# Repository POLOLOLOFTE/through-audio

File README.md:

# through-audio
a custom audio display for seeing how cool is music! compatible with the #free digital amp:

## Description
this is a machine that converts audio signals in visible immagines like a spectrum (Oscilloscope) or a frequencess dividor so you can see the music and admire the beauty of sound!

the hole mashine is controlled by a esp32 though a custom pcb

and it has got two displays: one with led matrix and the other one is a lcd display RGB 3.5" (for using the code it needs to be touch)

> "Note:" This is not a professional equipment and probably is not precise eather.

### why i made it?
as i sayed in the other projects i love music and it's a partof me, and have the opportunity to see it is a magic things!

## Assembly:
- you have to soder every componets to the pcb in the right order
- then you have to put the ESP32 DevC 38Pin in the slot
- after you could upload the firmware (opsional)
- then i raccomend wire up the display by folowing the pcb and then test is something explode😭🤣(just joking) i mean if it works!
- after this you should put the board on the custom case and rewire (use long wires) the displays (and glue them with hot glue)
- after this if you use the display that i will link you should run two wires from the matrix display's button and connect them to a second one and put the second on the front pannel
- then you should connect the 16v power, the usb (only for power) and the jack for the input
- enjoy!

## Input and Output
it has got only input:
- Jack
- 16V screw connector
- and USB (Esp32)

## Settings
it's not that complex but if you use the Default firmware you got the touch on the main display and the button for changing the mode on the odter matrix display
as the Default code you have 3 buttons that you can press 1 is for the theme (colors) one is for the mode that you want(Oscilloscope, equalizor, equalizor matrix like)

# Gallery:

#Bill Of Materials

| # | Component | Qty | Why it is used | Amazon link | Approx. price (USD) |
|---|-----------|-----|----------------|-------------|---------------------|
| 1 | ESP32 DevKit, 38-pin, USB-C (ESP-WROOM-32) | 1 | Main microcontroller. Samples the audio on ADC1 (GPIO34/35), computes the FFT and draws the three display modes. | [DIYables ESP32 38-pin](https://www.amazon.com/dp/B0GQXZ2RK1) | ~$11 |
| 2 | 3.5" TFT 480x320, ILI9488, SPI, resistive touch (stylus included) | 1 | User interface: oscilloscope, spectrum and stereo LED views, with big touch buttons for mode, color and gain. | [Hosyond 3.5" ILI9488](https://www.amazon.com/dp/B0BWJHK4M6) | ~$18 |
| 3 | Dual 12-level stereo LED VU-meter module (7-12 V) | 1 | Hardware LED level bars. They run on their own chip, so they need no GPIO, only the audio signal and 9 V. | [Dual 12-level VU meter](https://www.amazon.com/dp/B01MSYKM52) | ~$10 |
| 4 | L7809CV 9 V linear regulator, TO-220 (pack of 5) | 1 pack | Steps 16 V down to the 9 V the VU-meter needs (about 0.7 W of heat at 100 mA). | [L7809CV x5](https://www.amazon.com/dp/B08JHGS3LT) | ~$9 |
| 5 | LM2596 buck converter module (adjustable) | 1 | Efficient 16 V to 5 V for the ESP32 (VIN) and the display. Set it to 5.0 V with a multimeter before connecting anything. | [LM2596 buck module](https://www.amazon.com/dp/B01MS4D2FO) | ~$7 |
| 6 | 3.5 mm stereo jack, 5-pin PCB mount PJ-313 (pack of 5) | 1 pack | Audio input (left/right) for the ESP32 ADC and the VU-meter. | [uxcell PJ-313 x5](https://www.amazon.com/dp/B0BJJGXSJP) | ~$6 |
| 7 | 5.08 mm screw terminal blocks, 2-pin and 5-pin kit | 1 kit | 2-pin: 16 V power input. 5-pin: connection to the VU-meter (L, G, R, G, U). | [Terminal block kit](https://www.amazon.com/dp/B0F7Y1XMWT) | ~$11 |
| 8 | Metal film resistor assortment, 1/4 W 1% | 1 kit | 2x 100 kΩ (audio bias divider), 2x 1 kΩ (ADC input protection), 2x 1-10 kΩ (VU-meter inputs). | [BOJACK resistor kit](https://www.amazon.com/dp/B07P3MFG5D) | ~$13 |
| 9 | Electrolytic capacitor assortment (1 µF to 1000 µF) | 1 kit | Input and output smoothing for the 9 V regulator, and the 16 V input reservoir. Use 25 V or higher. | [Electrolytic kit](https://www.amazon.com/dp/B098RMS3S5) | ~$13 |
| 10 | Ceramic capacitor assortment (0.1 µF to 10 µF) | 1 kit | 100 nF decoupling for the regulator, 1-10 µF audio coupling and bias-node capacitors. | [BOJACK ceramic kit](https://www.amazon.com/dp/B07P7HRGT9) | ~$10 |
| 11 | 2.54 mm single-row female header strips, 40-pin (pack of 20) | 1 pack | Sockets for the ESP32 board and the display, so nothing is soldered directly. Cut to length. | [Female headers 1x40](https://www.amazon.com/dp/B0GXKSB3VF) | ~$8 |
| 12 | TO-220 heatsink + mounting kit (optional) | 1 pack | Keeps the L7809 cool if the VU-meter runs for long periods. | [TO-220 heatsink kit](https://www.amazon.com/dp/B078ZXZ1GN) | ~$8 |

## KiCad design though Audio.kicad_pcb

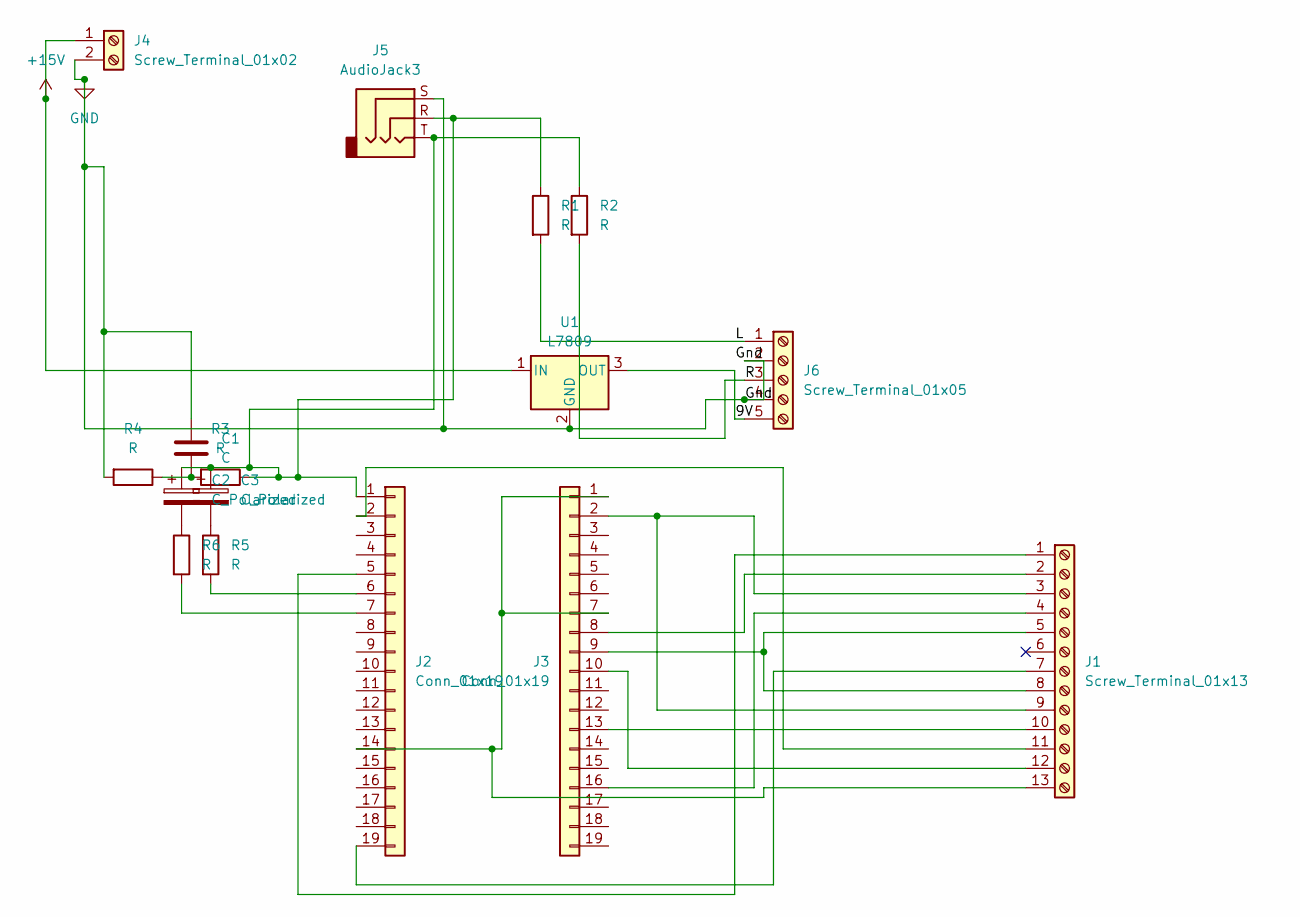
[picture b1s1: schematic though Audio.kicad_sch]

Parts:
C1: C; C_Rect_L18.0mm_W7.0mm_P15.00mm_FKS3_FKP3
C2, C3: C_Polarized; CP_Radial_Tantal_D5.0mm_P5.00mm
J1: Screw_Terminal_01x13; TerminalBlock_MaiXu_MX126-5.0-13P_1x13_P5.00mm
J2, J3: Conn_01x19; PinHeader_1x19_P2.54mm_Vertical
J4: Screw_Terminal_01x02; TerminalBlock_MaiXu_MX126-5.0-02P_1x02_P5.00mm
J5: AudioJack3; Jack_3.5mm_CUI_SJ1-3523N_Horizontal
J6: Screw_Terminal_01x05; TerminalBlock_MaiXu_MX126-5.0-05P_1x05_P5.00mm
R1, R2, R3, R4, R5, R6: R; R_Axial_DIN0207_L6.3mm_D2.5mm_P10.16mm_Horizontal
U1: L7809; TO-220-3_Vertical

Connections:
+15V: J4.1, U1.1 (IN)
/9V: J6.5, U1.3 (OUT)
/L: J6.1, R1.2
/R: J6.3, R2.2
GND: C1.1, J4.2, J5.S, J6.2, J6.4, R4.2, U1.2 (GND)
unnamed: C1.2, R3.2, R4.1
unnamed: C2.2, R6.1
unnamed: C3.2, R5.1
unnamed: J1.1, J2.5
unnamed: J1.2, J3.8
unnamed: J1.3, J1.9, J3.2
unnamed: J1.4, J3.16
unnamed: J1.5, J1.8, J3.9
unnamed: J1.7, J2.19
unnamed: J1.10, J3.13
unnamed: J1.11, J2.2
unnamed: J1.12, J3.10
unnamed: J1.13, J2.14, J3.1, J3.7
unnamed: C2.1, C3.1, J2.1, J5.R, J5.T, R1.1, R2.1, R3.1
unnamed: J2.6, R5.2
unnamed: J2.7, R6.2

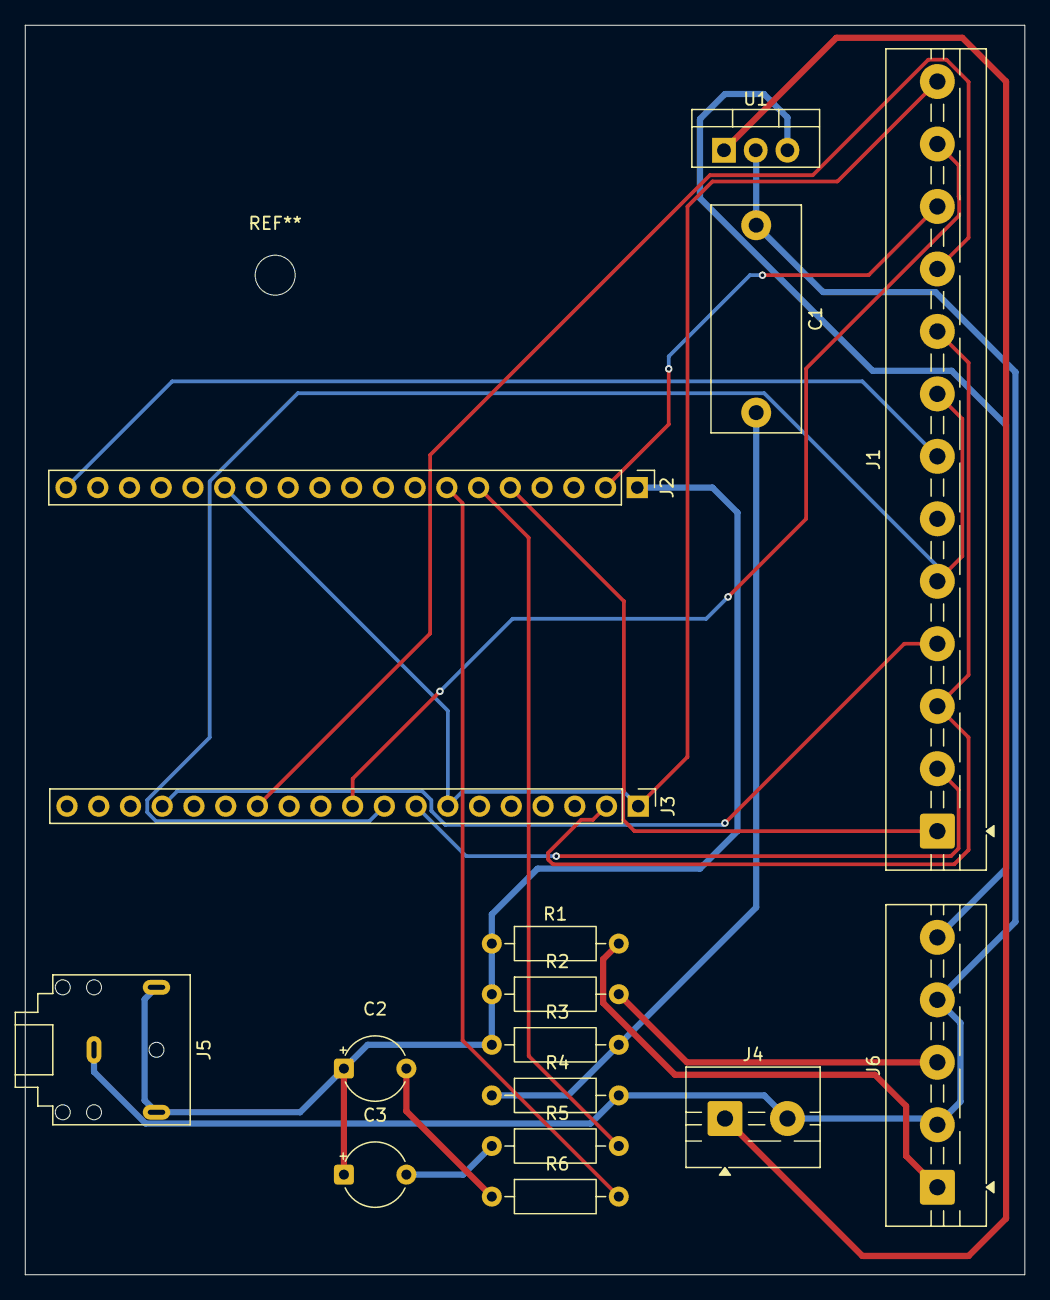
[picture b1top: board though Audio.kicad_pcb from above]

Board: 2 copper layers, 80.0 x 100.0 mm, 16 parts (0 on the bottom side), 21 nets.
